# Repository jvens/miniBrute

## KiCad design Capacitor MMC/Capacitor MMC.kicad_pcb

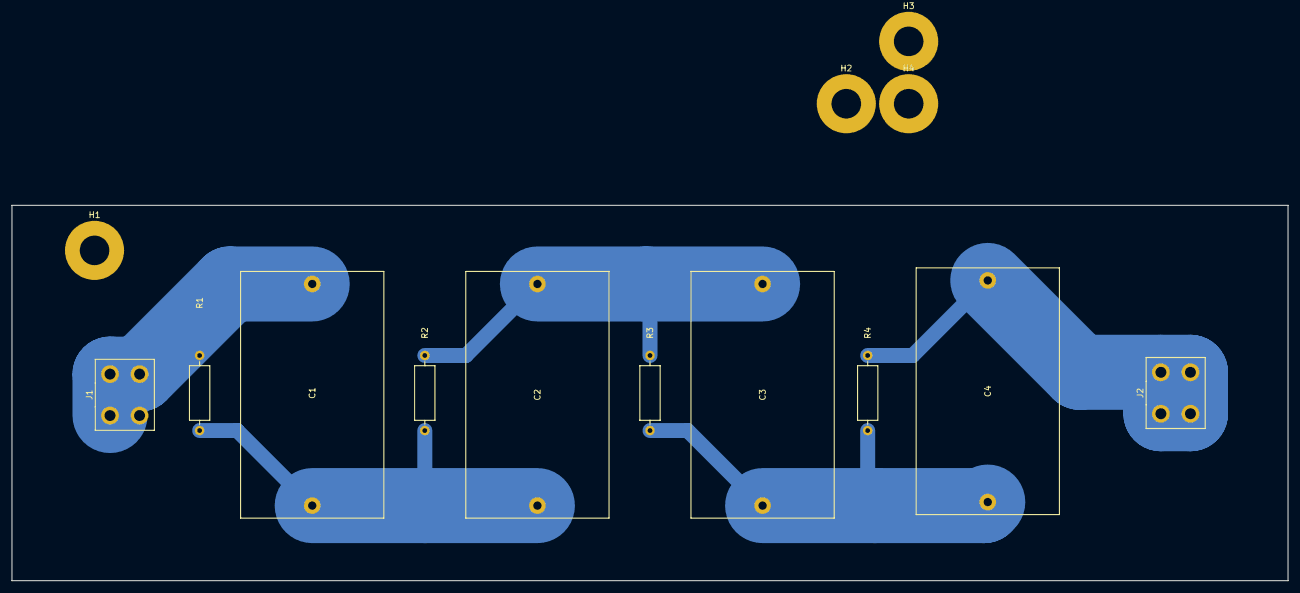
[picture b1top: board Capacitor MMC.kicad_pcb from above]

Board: 2 copper layers, 215.9 x 63.5 mm, 14 parts (0 on the bottom side), 5 nets.

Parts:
C1, C2, C3, C4: 0.33uF; C_Rect_L41.5mm_W24.0mm_P37.50mm_MKS4
H1, H2, H3, H4: MountingHole; MountingHole_5mm_Pad
J1, J2: Screw_Terminal_01x01; ScrewTerminal
R1, R2, R3, R4: 10M; R_Axial_DIN0309_L9.0mm_D3.2mm_P12.70mm_Horizontal

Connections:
unnamed: C1.1, C2.2, R1.1, R2.2
unnamed: C1.2, J1.1, R1.2
unnamed: C2.1, C3.2, R2.1, R3.2
unnamed: C3.1, C4.2, R3.1, R4.2
unnamed: C4.1, J2.1, R4.1

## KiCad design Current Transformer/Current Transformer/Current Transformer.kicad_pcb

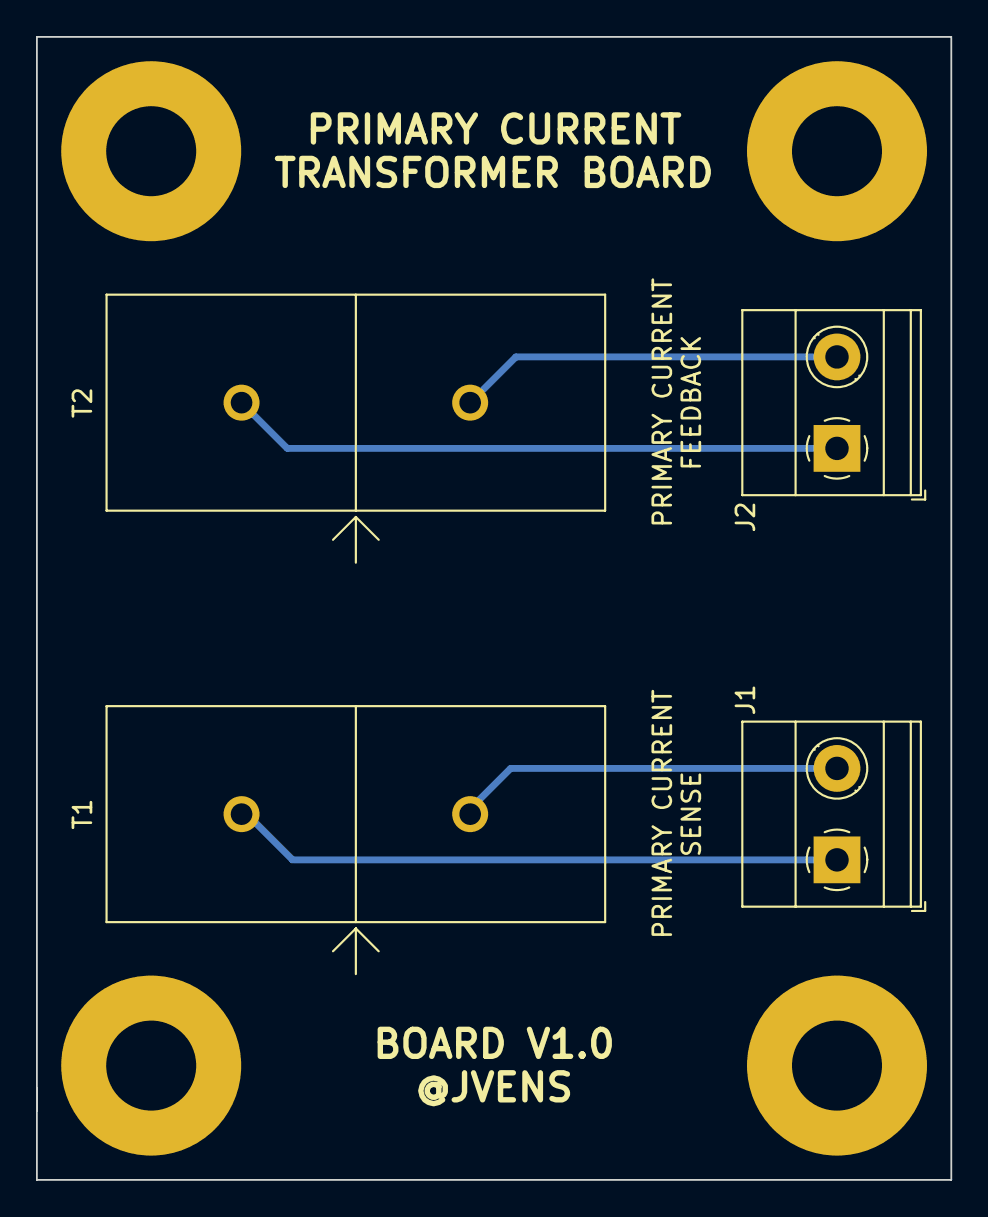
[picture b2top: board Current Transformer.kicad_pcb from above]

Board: 2 copper layers, 50.8 x 63.5 mm, 8 parts (0 on the bottom side), 4 nets.

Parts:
H1, H2, H3, H4: MountingHole; MountingHole_5mm_Pad
J1, J2: Screw_Terminal_01x02; TerminalBlock_Phoenix_MKDS-1,5-2-5.08_1x02_P5.08mm_Horizont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
T1, T2: CST206-1A

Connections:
unnamed: J1.1, T1.1
unnamed: J1.2, T1.2
unnamed: J2.1, T2.1
unnamed: J2.2, T2.2

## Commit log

2018-11-06 create project
2019-05-24 progress
2019-08-25 fix pin number on UCC37322D
2019-08-28 add low voltage power project
2019-08-28 add mounting holes to capacitor board
